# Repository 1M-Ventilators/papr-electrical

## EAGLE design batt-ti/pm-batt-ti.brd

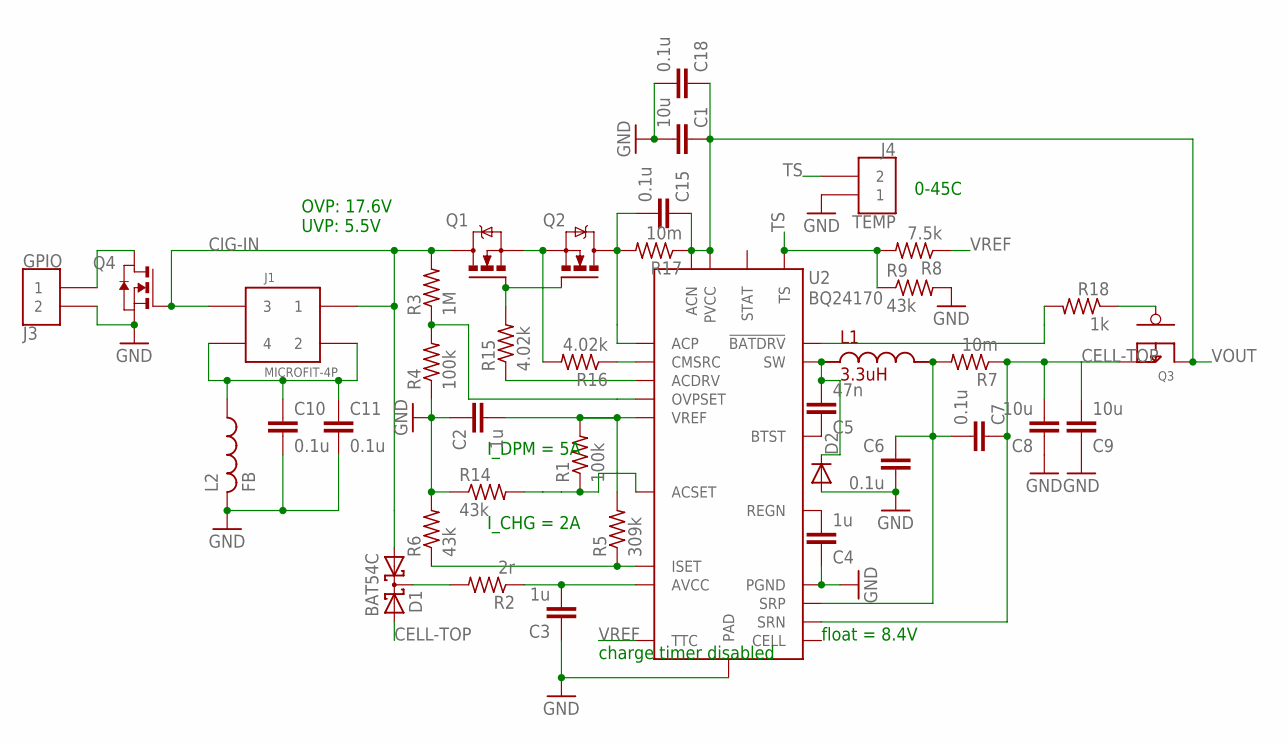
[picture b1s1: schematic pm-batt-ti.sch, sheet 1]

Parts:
C1: 10u; C1206
C2, C3, C4: 1u; C0603
C5: 47n; C0603
C6, C7, C10, C11, C15, C18: 0.1u; C0603
C8, C9: 10u; C0805
D1: BAT54C; SOT23
D2: DIODESMA-ALT; SMA-DIODE_ALT
J1: MICROFIT-4P
J3: GPIO; MICROFIT-2P
J4: TEMP; MICROFIT-2P
L1: 3.3uH; L-VISHAY-IHLP2020CZ01
L2: FB; L3216C
Q1, Q2: FDB047N10; D2_PAK
Q3: SUM110P; D2_PAK
Q4: NMOSSOT23; SOT-23
R1, R4: 100k; R0603
R2: 2r; R0603
R3: 1M; R0603
R5: 309k; R0603
R6, R9, R14: 43k; R0603
R7, R17: 10m; R0805
R8: 7.5k; R0603
R15, R16: 4.02k; R0603
R18: 1k; R0603
U2: BQ24170; QFN-24-TP

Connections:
CELL-TOP: C7.1, C8.2, C9.2, D1.2 (A2), Q3.3 (S3), R7.1, U2.15 (SRN); also elsewhere on the board
CIG-IN: D1.1 (A1), J1.1, J1.3, Q1.4 (D), Q4.3 (G), R3.2
GND: C1.2, C2.1, C3.1, C4.1, C6.2, C8.1, C9.1, C10.2, C11.2, C18.2, D2.A, J3.P$2 (2), J4.P$1 (1), L2.2, Q4.2 (S), R4.1, R6.2, R9.2, R14.1, U2.22 (PGND), U2.23 (PGND), U2.TP (PAD); also elsewhere on the board
unnamed: C15.2, Q2.4 (D), R17.2, U2.6 (ACP)
unnamed: R3.1, R4.2, U2.18 (OVPSET)
unnamed: R1.1, R14.2, U2.17 (ACSET)
unnamed: C3.2, R2.1, U2.4 (AVCC)
unnamed: R5.1, R6.1, U2.13 (ISET)
unnamed: C4.2, U2.20 (REGN)
unnamed: C5.2, D2.C, L1.P$1, U2.1 (SW), U2.24 (SW)
unnamed: C5.1, U2.21 (BTST)
unnamed: C6.1, C7.2, L1.P$2, R7.2, U2.16 (SRP)
unnamed: D1.3 (CC), R2.2
unnamed: R18.2, U2.19 (!BATDRV)
unnamed: Q1.3 (S), Q2.3 (S), R16.2
unnamed: Q3.1 (G4), R18.1
unnamed: Q1.1 (G), Q2.1 (G), R15.2
unnamed: R15.1, U2.8 (ACDRV)
unnamed: R16.1, U2.7 (CMSRC)
unnamed: J3.P$1 (1), Q4.1 (D)
SHLD: C10.1, C11.1, J1.2, J1.4, L2.1
TS: J4.P$2 (2), R8.2, R9.1, U2.10 (TS)
VOUT: C1.1, C15.1, C18.1, Q3.4 (D8), R17.1, U2.2 (PVCC), U2.3 (PVCC), U2.5 (ACN); also elsewhere on the board
VREF: C2.2, R1.2, R5.2, R8.1, U2.11 (TTC), U2.12 (VREF)

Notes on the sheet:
I_DPM = 5A
float = 8.4V
charge timer disabled
OVP: 17.6V UVP: 5.5V
I_CHG = 2A
0-45C

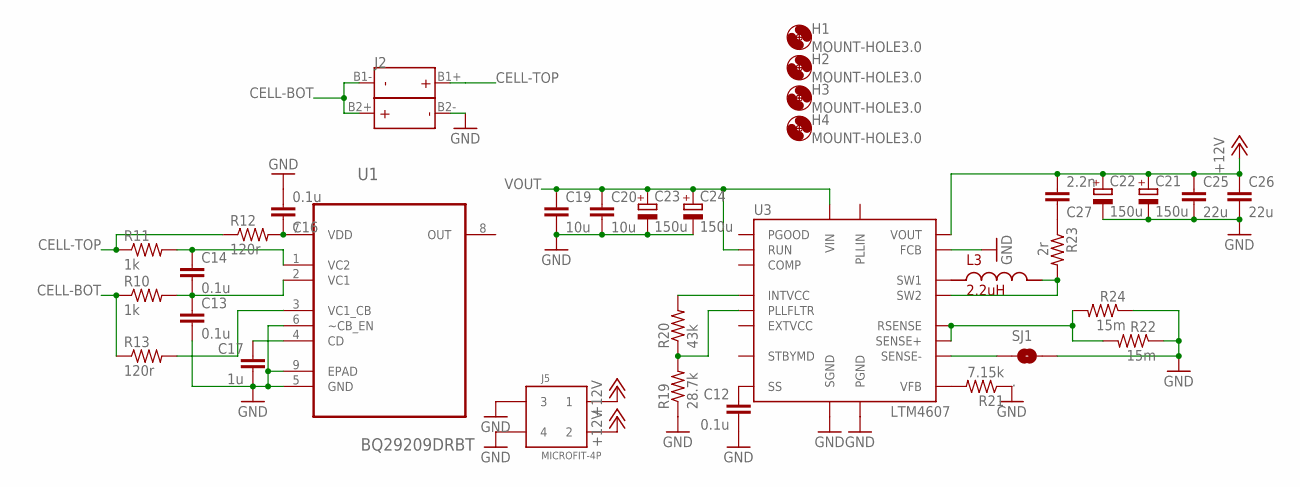
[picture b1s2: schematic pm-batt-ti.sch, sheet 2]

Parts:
C12: 0.1u; C0805
C13, C14, C16: 0.1u; C0603
C17: 1u; C0603
C19, C20: 10u; C1206
C21, C22, C23, C24: 150u; C2917
C25, C26: 22u; C1206
C27: 2.2n; C0603
H1, H2, H3, H4: MOUNT-HOLE3.0; 3,0
J2: 18650X2; K1048
J5: MICROFIT-4P
L3: 2.2uH; L-VISHAY-IHLP2020CZ01
R10, R11: 1k; R0603
R12, R13: 120r; R0603
R19: 28.7k; R0603
R20: 43k; R0603
R21: 7.15k; R0603
R22, R24: 15m; R0805@1
R23: 2r; R0603
SJ1: .; SJ_2S-TRACE
U1: BQ29209DRBT; SON65P315X315X100-9N
U3: LTM4607

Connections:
+12V: C21.+, C22.+, C25.1, C26.1, C27.2, J5.1, J5.2, U3.E1 (VOUT), U3.E2 (VOUT), U3.F1 (VOUT), U3.F2 (VOUT), U3.F3 (VOUT), U3.F4 (VOUT), U3.G1 (VOUT), U3.G2 (VOUT), U3.G3 (VOUT), U3.G4 (VOUT), U3.H1 (VOUT), U3.H2 (VOUT), U3.H3 (VOUT), U3.H4 (VOUT)
CELL-BOT: J2.B1-, J2.B2+, R10.1, R13.1
CELL-TOP: J2.B1+, R11.1, R12.1; also elsewhere on the board
GND: C12.2, C13.2, C16.2, C17.2, C19.2, C20.2, C21.-, C22.-, C23.-, C24.-, C25.2, C26.2, J2.B2-, J5.3, J5.4, R19.1, R21.1, R22.1, R24.1, SJ1.2, U1.5 (GND), U1.6 (~CB_EN), U1.9 (EPAD), U3.A1 (PGND), U3.A2 (PGND), U3.A3 (PGND), U3.A7 (SGND), U3.A9 (FCB), U3.A11 (PGND), U3.A12 (PGND), U3.B1 (PGND), U3.B2 (PGND), U3.B3 (PGND), U3.B4 (PGND), U3.B10 (PGND), U3.B11 (PGND), U3.B12 (PGND), U3.C1 (PGND), U3.C2 (PGND), U3.C3 (PGND), U3.C4 (PGND), U3.C5 (PGND), U3.C6 (PGND), U3.C7 (PGND), U3.C8 (PGND), U3.C9 (PGND), U3.C10 (PGND), U3.C11 (PGND), U3.C12 (PGND), U3.D1 (PGND), U3.D2 (PGND), U3.D3 (PGND), U3.D4 (PGND), U3.D5 (PGND), U3.D6 (PGND), U3.D7 (PGND), U3.D8 (PGND), U3.D9 (PGND), U3.D10 (PGND), U3.D11 (PGND), U3.D12 (PGND), U3.E3 (PGND), U3.E4 (PGND), U3.E5 (PGND), U3.E6 (PGND), U3.E7 (PGND), U3.E8 (PGND), U3.E9 (PGND), U3.E10 (PGND), U3.E11 (PGND), U3.E12 (PGND); also elsewhere on the board
unnamed: C17.1, U1.4 (CD)
unnamed: R19.2, R20.1, U3.B8 (PLLFLTR)
unnamed: L3.P$1, U3.J1 (SW1), U3.J2 (SW1), U3.J3 (SW1), U3.J4 (SW1), U3.K1 (SW1), U3.K2 (SW1), U3.K3 (SW1), U3.K4 (SW1), U3.L1 (SW1), U3.L2 (SW1), U3.L3 (SW1), U3.L4 (SW1), U3.M1 (SW1), U3.M2 (SW1), U3.M3 (SW1), U3.M4 (SW1)
unnamed: C13.1, C14.2, R10.2, U1.2 (VC1)
unnamed: C14.1, R11.2, U1.1 (VC2)
unnamed: R20.2, U3.F5 (INTVCC)
unnamed: C16.1, R12.2, U1.7 (VDD)
unnamed: R13.2, U1.3 (VC1_CB)
unnamed: C12.1, U3.A6 (SS)
unnamed: R21.2, U3.B6 (VFB)
unnamed: C27.1, R23.1
unnamed: SJ1.1, U3.A5 (SENSE-)
RSENSE: R22.2, R24.2, U3.A4 (SENSE+), U3.F10 (RSENSE), U3.F11 (RSENSE), U3.F12 (RSENSE), U3.G5 (RSENSE), U3.G6 (RSENSE), U3.G7 (RSENSE), U3.G8 (RSENSE), U3.G9 (RSENSE), U3.G10 (RSENSE), U3.G11 (RSENSE), U3.G12 (RSENSE), U3.H5 (RSENSE), U3.H6 (RSENSE), U3.H7 (RSENSE), U3.H8 (RSENSE), U3.H9 (RSENSE), U3.H10 (RSENSE), U3.H11 (RSENSE), U3.H12 (RSENSE), U3.J5 (RSENSE), U3.J6 (RSENSE), U3.J7 (RSENSE), U3.K5 (RSENSE), U3.K6 (RSENSE), U3.L5 (RSENSE), U3.L6 (RSENSE), U3.M5 (RSENSE), U3.M6 (RSENSE)
SW2: L3.P$2, R23.2, U3.J8 (SW2), U3.J9 (SW2), U3.K7 (SW2), U3.K8 (SW2), U3.K9 (SW2), U3.L7 (SW2), U3.L8 (SW2), U3.L9 (SW2), U3.M7 (SW2), U3.M8 (SW2), U3.M9 (SW2)
VOUT: C19.1, C20.1, C23.+, C24.+, U3.A8 (RUN), U3.J10 (VIN), U3.J11 (VIN), U3.J12 (VIN), U3.K10 (VIN), U3.K11 (VIN), U3.K12 (VIN), U3.L10 (VIN), U3.L11 (VIN), U3.L12 (VIN), U3.M10 (VIN), U3.M11 (VIN), U3.M12 (VIN); also elsewhere on the board

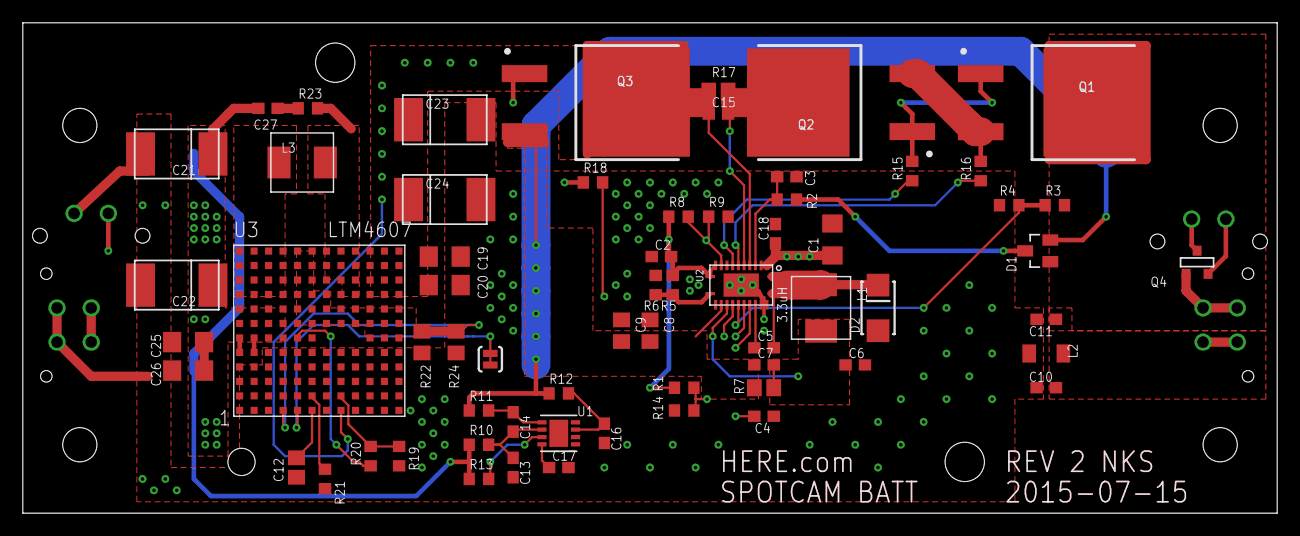
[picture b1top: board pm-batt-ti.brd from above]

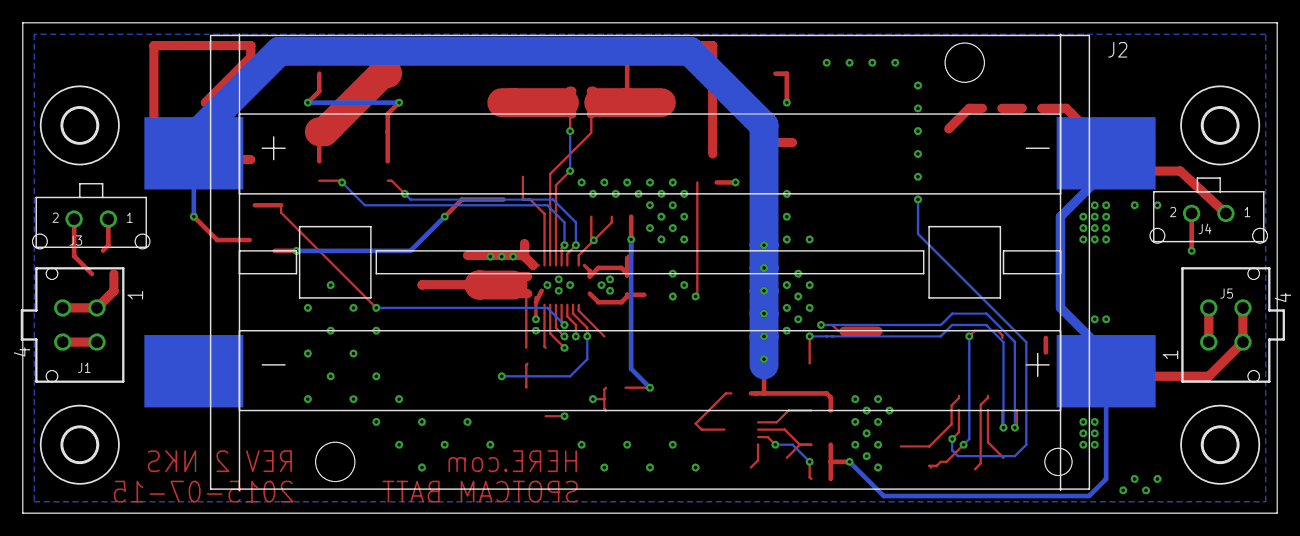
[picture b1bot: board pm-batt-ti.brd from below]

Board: 4 copper layers, 110.0 x 43.0 mm, 73 parts (9 on the bottom side), 40 nets.

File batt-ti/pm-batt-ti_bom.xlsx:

Item # | Qty | Part | Package | Tech. | Description | Vendor | Vendor P/N | Manufacturer | Manufacturer P/N:
1 | 5 | C1; C8-C9; C19-C20 | 1206 | SMT | 10u, Ceramic, 10%, 50V, X5R | Digikey | 445-5998-1-ND | TDK Corporation | C3216X5R1H106K160AB
2 | 4 | C2-C4; C17 | 603 | SMT | 1u, Ceramic, 10%, 50V, X5R | Digikey | 445-7468-1-ND | TDK Corporation | C1608X5R1H105K080AB
3 | 1 | C5 | 603 | SMT | 47n, Ceramic, 10%, 50V, X5R | Digikey | 445-14155-1-ND | TDK Corporation | C1608X5R1H473K080AA
4 | 10 | C6-C7; C10-C16; C18 | 603 | SMT | 0.1u, Ceramic, 10%, 50V, X5R | Digikey | 445-7456-1-ND | TDK Corporation | C1608X5R1H104K080AA
5 | 4 | C21-C24 | 2917 | SMT | 150u, Tantalum, 10%, 16V | Digikey | 718-1494-1-ND | Vishay Sprague | TR3D157K016C0100
6 | 2 | C25-C26 | 1206 | SMT | 22u, Ceramic, 20%, 35V, X5R | Digikey | 445-8045-1-ND | TDK Corporation | C3216X5R1V226M160AC
7 | 1 | C27 | 603 | SMT | 2.2n, Ceramic, 10%, 50V, C0G | Digikey | 445-13978-1-ND | TDK Corporation | C1608C0G1H222K080AA
8 | 1 | D1 | SOT-23 | SMT | Dual Schottky Common Cathode | Digikey | BAT54CFSCT-ND | Fairchild Semi | BAT54C
9 | 1 | D2 | SMA | SMT | Power Schottky, 0.45V/40V, 3A | Digikey | B340LA-FDICT-ND | Diodes Inc | B340LA-13-F
10 | 2 | J1; J5 | 2 x 2 - 3mm | PTH | Microfit 4-pin - Power In & Out | Digikey | WM1796-ND | Molex Inc | 43045-0414
11 | 1 | J2 | 2 x 18650 | SMT | 2-cell 18650 Battery Holder | Digikey | 36-1048-ND | Keystone | 1048
12 | 2 | J3; J4 | 2 x 1 - 3mm | PTH | Microfit 2-pin - Temp & Vsense | Digikey | WM1922-ND | Molex Inc | 43650-0216
13 | 1 | L1 | NONSTD | SMT | 3.3uH, 5A/54.7m, Shielded, 20% | Digikey | 541-1269-1-ND | Vishay Dale | IHLP2020CZER3R3M01
14 | 1 | L2 | 1206 | SMT | Ferrite Chip, 6A, 0.018 ohm | Digikey | 240-2411-1-ND | Laird | HI1206T161R-10
15 | 1 | L3 | NONSTD | SMT | 2.2uH, 5.8A/29.2m, Shielded, 20% | Digikey | 541-1268-1-ND | Vishay Dale | IHLP2020CZER2R2M01
16 | 2 | Q1-Q2 | D2-PAK | SMT | N-Channel PowerTrench MOSFET | Digikey | FDB047N10CT-ND | Fairchild Semi | FDB047N10
17 | 1 | Q3 | D2-PAK | SMT | PMOS, 60V, 110A, 3.75W | Digikey | SUM110P06-07L-E3CT-ND | Vishay Siliconix | SUM110P06-07L-E3
18 | 1 | Q4 | SOT-23 | SMT | NMOS, 30V, 0.3A, 0.35W | Digikey | 2N7002KCT-ND | Fairchild Semi | 2N7002K
19 | 2 | R1; R4 | 603 | SMT | 100k, Thick Film, 1%, 1/4 W | Digikey | P100KBYCT-ND | Panasonic | ERJ-PA3F1003V
20 | 2 | R2; R23 | 603 | SMT | 2r, Thick Film, 5%, 1/4 W | Digikey | P2.00BZCT-ND | Panasonic | ERJ-PA3J2R0V
21 | 1 | R3 | 603 | SMT | 1M, Thick Film, 1%, 1/4 W | Digikey | P1.0MBYCT-ND | Panasonic | ERJ-PA3F1004V
22 | 1 | R5 | 603 | SMT | 309k, Thin Film, 0.1%, 1/6 W | Digikey | A110347CT-ND | TE Connectivity | 3-2176090-7
23 | 4 | R6; R9; R14; R20 | 603 | SMT | 43k, Thick Film, 1%, 1/4 W | Digikey | P43KBYCT-ND | Panasonic | ERJ-PA3F4302V
24 | 2 | R7; R17 | 805 | SMT | 10m, Thick Film, 1%, 1/2 W | Digikey | P.01AQCT-ND | Panasonic | ERJ-6BWFR010V
25 | 1 | R8 | 603 | SMT | 7.5k, Thick Film, 1%, 1/4 W | Digikey | P7.5KBYCT-ND | Panasonic | ERJ-PA3F7501V
26 | 3 | R10-R11; R18 | 603 | SMT | 1k, Thick Film, 1%, 1/4 W | Digikey | P1.0KBYCT-ND | Panasonic | ERJ-PA3F1001V
27 | 2 | R12-R13 | 603 | SMT | 120r, Thick Film, 1%, 1/4 W | Digikey | P120BYCT-ND | Panasonic | ERJ-PA3F1200V
28 | 2 | R15-R16 | 603 | SMT | 4.02k, Thin Film, 0.1%, 1/6 W | Digikey | A110166CT-ND | TE Connectivity | 6-2176088-4
29 | 1 | R19 | 603 | SMT | 28.7k, Thin Film, 0.1%, 1/6 W | Digikey | A110248CT-ND | TE Connectivity | 4-2176089-0
30 | 1 | R21 | 603 | SMT | 7.15k, Thin Film, 0.1%, 1/6 W | Digikey | A110190CT-ND | TE Connectivity | 8-2176088-7
31 | 2 | R22; R24 | 805 | SMT | 15m, Thick Film, 1%, 1/2 W | Digikey | P.015AQCT-ND | Panasonic | ERJ-6BWFR015V
32 | 1 | U1 | SON-8-EP | SMT | BQ29209 Battery OVP & Balancer | Digikey | 296-27677-1-ND | Texas Instruments | BQ29209DRBR
33 | 1 | U2 | QFN-24-TP | SMT | BQ24170 Battery Charger / Manager | Digikey | 296-28049-1-ND | Texas Instruments | BQ24170RGYT
34 | 1 | U3 | LGA-141 | SMT | LTM4607 12V Boost IC | Digikey | LTM4607EV#PBF-ND | Linear | LTM4607EV#PBF

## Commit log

2020-04-03 initial commit. adding sample cam/lbr/etc, as well as sample circuit

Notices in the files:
parts and their libraries:
SparkFun-Passives: Licensing: CC v3.0 Share-Alike You are welcome to use this library for commercial purposes.
